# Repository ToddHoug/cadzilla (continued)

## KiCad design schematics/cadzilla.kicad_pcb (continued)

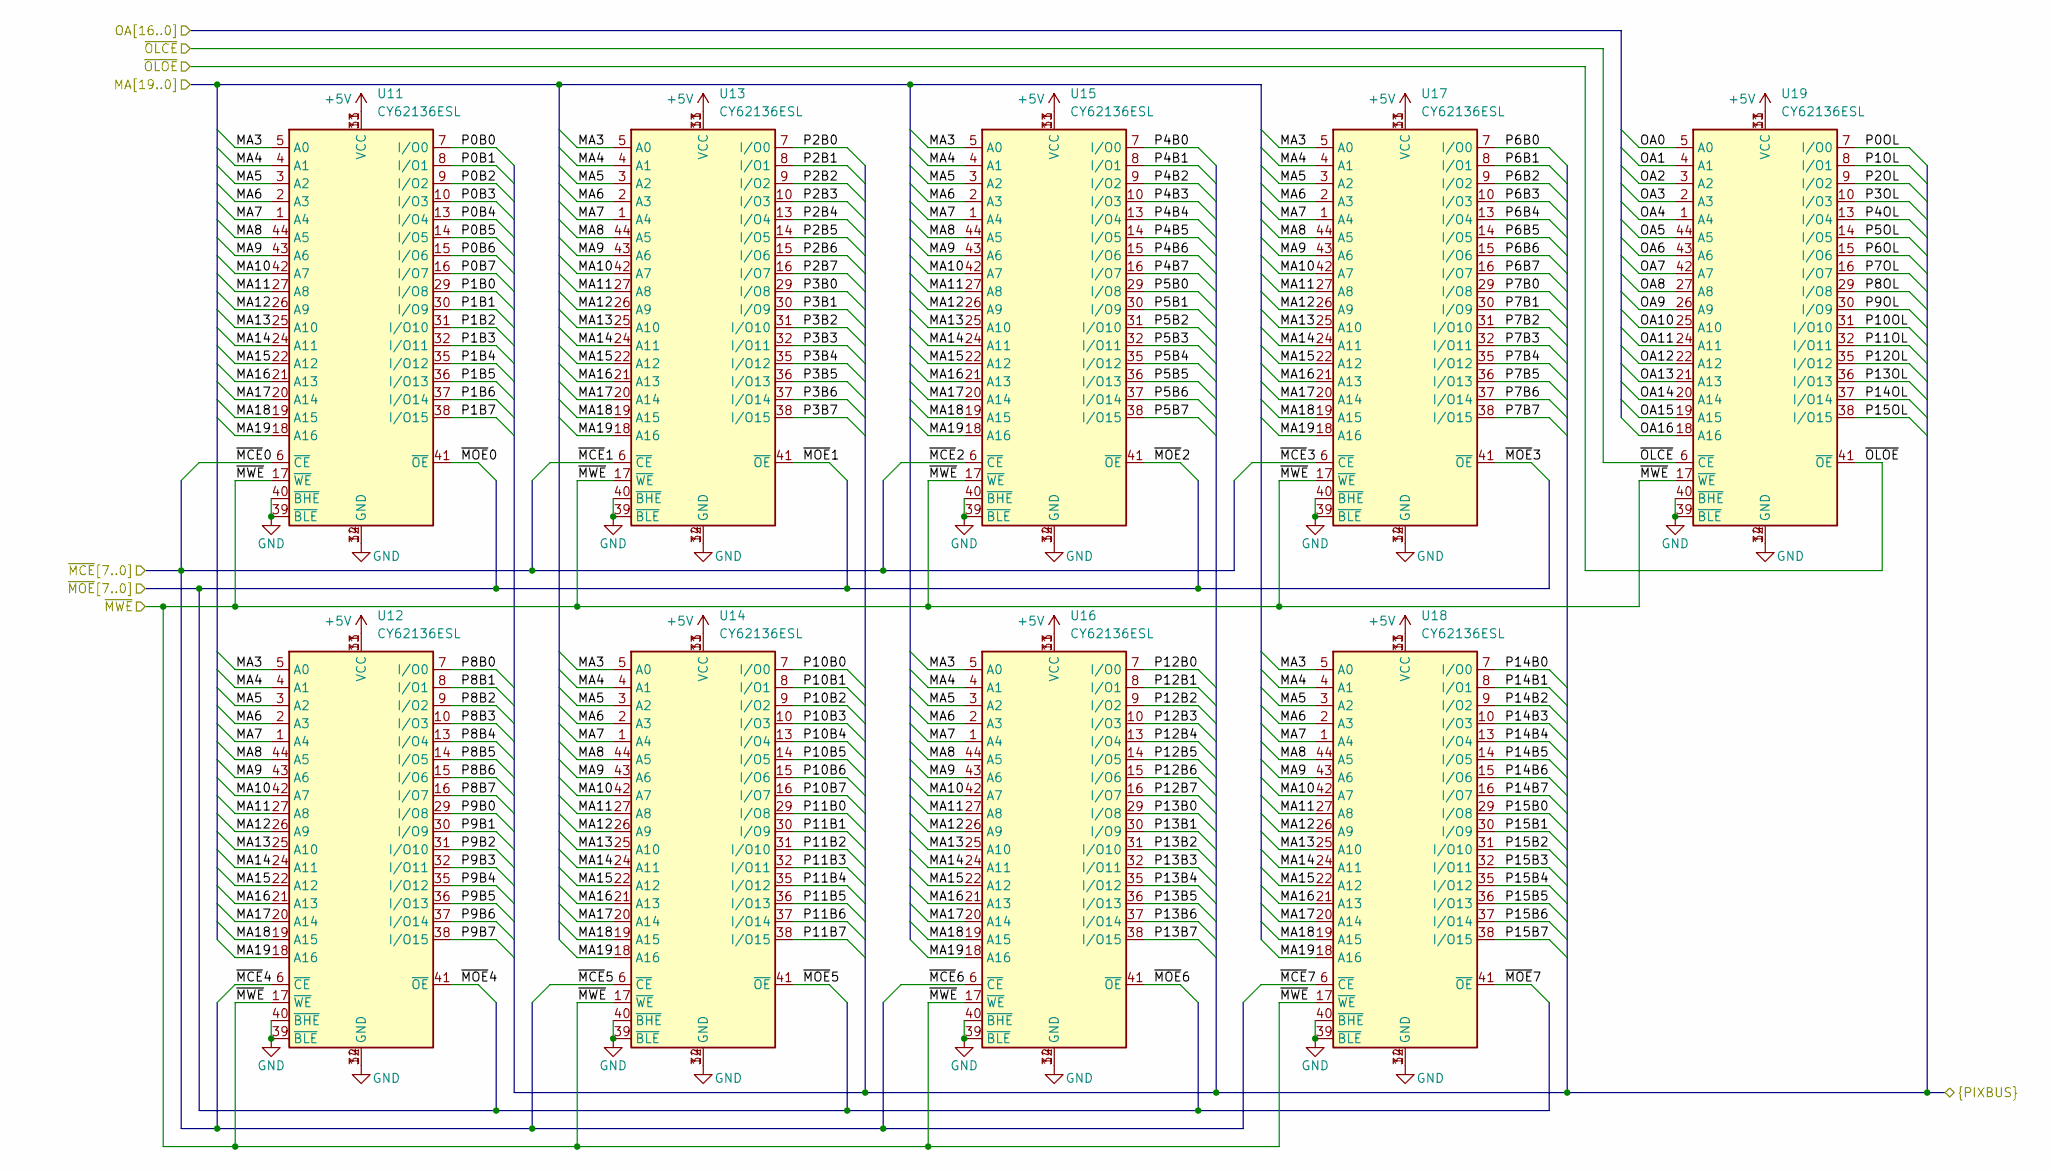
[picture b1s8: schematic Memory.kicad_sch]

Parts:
U11, U12, U13, U14, U15, U16, U17, U18, U19: CY62136ESL; TSOP-II-44_10.16x18.41mm_P0.8mm

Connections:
+5V: U11.11 (VCC), U11.33 (VCC), U12.11 (VCC), U12.33 (VCC), U13.11 (VCC), U13.33 (VCC), U14.11 (VCC), U14.33 (VCC), U15.11 (VCC), U15.33 (VCC), U16.11 (VCC), U16.33 (VCC), U17.11 (VCC), U17.33 (VCC), U18.11 (VCC), U18.33 (VCC), U19.11 (VCC), U19.33 (VCC); also elsewhere on the board
/Data Buffers/P0B0: U11.7 (I/O0); also elsewhere on the board
/Data Buffers/P0B1: U11.8 (I/O1); also elsewhere on the board
/Data Buffers/P0B2: U11.9 (I/O2); also elsewhere on the board
/Data Buffers/P0B3: U11.10 (I/O3); also elsewhere on the board
/Data Buffers/P0B4: U11.13 (I/O4); also elsewhere on the board
/Data Buffers/P0B5: U11.14 (I/O5); also elsewhere on the board
/Data Buffers/P0B6: U11.15 (I/O6); also elsewhere on the board
/Data Buffers/P0B7: U11.16 (I/O7); also elsewhere on the board
/Data Buffers/P0OL: U19.7 (I/O0); also elsewhere on the board
/Data Buffers/P1B0: U11.29 (I/O8); also elsewhere on the board
/Data Buffers/P1B1: U11.30 (I/O9); also elsewhere on the board
/Data Buffers/P1B2: U11.31 (I/O10); also elsewhere on the board
/Data Buffers/P1B3: U11.32 (I/O11); also elsewhere on the board
/Data Buffers/P1B4: U11.35 (I/O12); also elsewhere on the board
/Data Buffers/P1B5: U11.36 (I/O13); also elsewhere on the board
/Data Buffers/P1B6: U11.37 (I/O14); also elsewhere on the board
/Data Buffers/P1B7: U11.38 (I/O15); also elsewhere on the board
/Data Buffers/P1OL: U19.8 (I/O1); also elsewhere on the board
/Data Buffers/P2B0: U13.7 (I/O0); also elsewhere on the board
/Data Buffers/P2B1: U13.8 (I/O1); also elsewhere on the board
/Data Buffers/P2B2: U13.9 (I/O2); also elsewhere on the board
/Data Buffers/P2B3: U13.10 (I/O3); also elsewhere on the board
/Data Buffers/P2B4: U13.13 (I/O4); also elsewhere on the board
/Data Buffers/P2B5: U13.14 (I/O5); also elsewhere on the board
/Data Buffers/P2B6: U13.15 (I/O6); also elsewhere on the board
/Data Buffers/P2B7: U13.16 (I/O7); also elsewhere on the board
/Data Buffers/P2OL: U19.9 (I/O2); also elsewhere on the board
/Data Buffers/P3B0: U13.29 (I/O8); also elsewhere on the board
/Data Buffers/P3B1: U13.30 (I/O9); also elsewhere on the board
/Data Buffers/P3B2: U13.31 (I/O10); also elsewhere on the board
/Data Buffers/P3B3: U13.32 (I/O11); also elsewhere on the board
/Data Buffers/P3B4: U13.35 (I/O12); also elsewhere on the board
/Data Buffers/P3B5: U13.36 (I/O13); also elsewhere on the board
/Data Buffers/P3B6: U13.37 (I/O14); also elsewhere on the board
/Data Buffers/P3B7: U13.38 (I/O15); also elsewhere on the board
/Data Buffers/P3OL: U19.10 (I/O3); also elsewhere on the board
/Data Buffers/P4B0: U15.7 (I/O0); also elsewhere on the board
/Data Buffers/P4B1: U15.8 (I/O1); also elsewhere on the board
/Data Buffers/P4B2: U15.9 (I/O2); also elsewhere on the board
/Data Buffers/P4B3: U15.10 (I/O3); also elsewhere on the board
/Data Buffers/P4B4: U15.13 (I/O4); also elsewhere on the board
/Data Buffers/P4B5: U15.14 (I/O5); also elsewhere on the board
/Data Buffers/P4B6: U15.15 (I/O6); also elsewhere on the board
/Data Buffers/P4B7: U15.16 (I/O7); also elsewhere on the board
/Data Buffers/P4OL: U19.13 (I/O4); also elsewhere on the board
/Data Buffers/P5B0: U15.29 (I/O8); also elsewhere on the board
/Data Buffers/P5B1: U15.30 (I/O9); also elsewhere on the board
/Data Buffers/P5B2: U15.31 (I/O10); also elsewhere on the board
/Data Buffers/P5B3: U15.32 (I/O11); also elsewhere on the board
/Data Buffers/P5B4: U15.35 (I/O12); also elsewhere on the board
/Data Buffers/P5B5: U15.36 (I/O13); also elsewhere on the board
/Data Buffers/P5B6: U15.37 (I/O14); also elsewhere on the board
/Data Buffers/P5B7: U15.38 (I/O15); also elsewhere on the board
/Data Buffers/P5OL: U19.14 (I/O5); also elsewhere on the board
/Data Buffers/P6B0: U17.7 (I/O0); also elsewhere on the board
/Data Buffers/P6B1: U17.8 (I/O1); also elsewhere on the board
/Data Buffers/P6B2: U17.9 (I/O2); also elsewhere on the board
/Data Buffers/P6B3: U17.10 (I/O3); also elsewhere on the board
/Data Buffers/P6B4: U17.13 (I/O4); also elsewhere on the board
/Data Buffers/P6B5: U17.14 (I/O5); also elsewhere on the board
/Data Buffers/P6B6: U17.15 (I/O6); also elsewhere on the board
/Data Buffers/P6B7: U17.16 (I/O7); also elsewhere on the board
/Data Buffers/P6OL: U19.15 (I/O6); also elsewhere on the board
/Data Buffers/P7B0: U17.29 (I/O8); also elsewhere on the board
/Data Buffers/P7B1: U17.30 (I/O9); also elsewhere on the board
/Data Buffers/P7B2: U17.31 (I/O10); also elsewhere on the board
/Data Buffers/P7B3: U17.32 (I/O11); also elsewhere on the board
/Data Buffers/P7B4: U17.35 (I/O12); also elsewhere on the board
/Data Buffers/P7B5: U17.36 (I/O13); also elsewhere on the board
/Data Buffers/P7B6: U17.37 (I/O14); also elsewhere on the board
/Data Buffers/P7B7: U17.38 (I/O15); also elsewhere on the board
/Data Buffers/P7OL: U19.16 (I/O7); also elsewhere on the board
/Data Buffers/P8B0: U12.7 (I/O0); also elsewhere on the board
/Data Buffers/P8B1: U12.8 (I/O1); also elsewhere on the board
/Data Buffers/P8B2: U12.9 (I/O2); also elsewhere on the board
/Data Buffers/P8B3: U12.10 (I/O3); also elsewhere on the board
/Data Buffers/P8B4: U12.13 (I/O4); also elsewhere on the board
/Data Buffers/P8B5: U12.14 (I/O5); also elsewhere on the board
/Data Buffers/P8B6: U12.15 (I/O6); also elsewhere on the board
/Data Buffers/P8B7: U12.16 (I/O7); also elsewhere on the board
/Data Buffers/P8OL: U19.29 (I/O8); also elsewhere on the board
/Data Buffers/P9B0: U12.29 (I/O8); also elsewhere on the board
/Data Buffers/P9B1: U12.30 (I/O9); also elsewhere on the board
/Data Buffers/P9B2: U12.31 (I/O10); also elsewhere on the board
/Data Buffers/P9B3: U12.32 (I/O11); also elsewhere on the board
/Data Buffers/P9B4: U12.35 (I/O12); also elsewhere on the board
/Data Buffers/P9B5: U12.36 (I/O13); also elsewhere on the board
/Data Buffers/P9B6: U12.37 (I/O14); also elsewhere on the board
/Data Buffers/P9B7: U12.38 (I/O15); also elsewhere on the board
/Data Buffers/P9OL: U19.30 (I/O9); also elsewhere on the board
/Data Buffers/P10B0: U14.7 (I/O0); also elsewhere on the board
/Data Buffers/P10B1: U14.8 (I/O1); also elsewhere on the board
/Data Buffers/P10B2: U14.9 (I/O2); also elsewhere on the board
/Data Buffers/P10B3: U14.10 (I/O3); also elsewhere on the board
/Data Buffers/P10B4: U14.13 (I/O4); also elsewhere on the board
/Data Buffers/P10B5: U14.14 (I/O5); also elsewhere on the board
/Data Buffers/P10B6: U14.15 (I/O6); also elsewhere on the board
/Data Buffers/P10B7: U14.16 (I/O7); also elsewhere on the board
/Data Buffers/P10OL: U19.31 (I/O10); also elsewhere on the board
/Data Buffers/P11B0: U14.29 (I/O8); also elsewhere on the board
/Data Buffers/P11B1: U14.30 (I/O9); also elsewhere on the board
/Data Buffers/P11B2: U14.31 (I/O10); also elsewhere on the board
/Data Buffers/P11B3: U14.32 (I/O11); also elsewhere on the board
/Data Buffers/P11B4: U14.35 (I/O12); also elsewhere on the board
/Data Buffers/P11B5: U14.36 (I/O13); also elsewhere on the board
/Data Buffers/P11B6: U14.37 (I/O14); also elsewhere on the board
/Data Buffers/P11B7: U14.38 (I/O15); also elsewhere on the board
/Data Buffers/P11OL: U19.32 (I/O11); also elsewhere on the board
/Data Buffers/P12B0: U16.7 (I/O0); also elsewhere on the board
/Data Buffers/P12B1: U16.8 (I/O1); also elsewhere on the board
/Data Buffers/P12B2: U16.9 (I/O2); also elsewhere on the board
/Data Buffers/P12B3: U16.10 (I/O3); also elsewhere on the board
/Data Buffers/P12B4: U16.13 (I/O4); also elsewhere on the board
/Data Buffers/P12B5: U16.14 (I/O5); also elsewhere on the board
/Data Buffers/P12B6: U16.15 (I/O6); also elsewhere on the board
/Data Buffers/P12B7: U16.16 (I/O7); also elsewhere on the board
/Data Buffers/P12OL: U19.35 (I/O12); also elsewhere on the board
/Data Buffers/P13B0: U16.29 (I/O8); also elsewhere on the board
/Data Buffers/P13B1: U16.30 (I/O9); also elsewhere on the board
/Data Buffers/P13B2: U16.31 (I/O10); also elsewhere on the board
/Data Buffers/P13B3: U16.32 (I/O11); also elsewhere on the board
/Data Buffers/P13B4: U16.35 (I/O12); also elsewhere on the board
/Data Buffers/P13B5: U16.36 (I/O13); also elsewhere on the board
/Data Buffers/P13B6: U16.37 (I/O14); also elsewhere on the board
/Data Buffers/P13B7: U16.38 (I/O15); also elsewhere on the board
/Data Buffers/P13OL: U19.36 (I/O13); also elsewhere on the board
/Data Buffers/P14B0: U18.7 (I/O0); also elsewhere on the board
/Data Buffers/P14B1: U18.8 (I/O1); also elsewhere on the board
/Data Buffers/P14B2: U18.9 (I/O2); also elsewhere on the board
/Data Buffers/P14B3: U18.10 (I/O3); also elsewhere on the board
/Data Buffers/P14B4: U18.13 (I/O4); also elsewhere on the board
/Data Buffers/P14B5: U18.14 (I/O5); also elsewhere on the board
/Data Buffers/P14B6: U18.15 (I/O6); also elsewhere on the board
/Data Buffers/P14B7: U18.16 (I/O7); also elsewhere on the board
/Data Buffers/P14OL: U19.37 (I/O14); also elsewhere on the board
/Data Buffers/P15B0: U18.29 (I/O8); also elsewhere on the board
/Data Buffers/P15B1: U18.30 (I/O9); also elsewhere on the board
/Data Buffers/P15B2: U18.31 (I/O10); also elsewhere on the board
/Data Buffers/P15B3: U18.32 (I/O11); also elsewhere on the board
/Data Buffers/P15B4: U18.35 (I/O12); also elsewhere on the board
/Data Buffers/P15B5: U18.36 (I/O13); also elsewhere on the board
/Data Buffers/P15B6: U18.37 (I/O14); also elsewhere on the board
/Data Buffers/P15B7: U18.38 (I/O15); also elsewhere on the board
/Data Buffers/P15OL: U19.38 (I/O15); also elsewhere on the board
/Memory Interface/MA3: U11.5 (A0), U12.5 (A0), U13.5 (A0), U14.5 (A0), U15.5 (A0), U16.5 (A0), U17.5 (A0), U18.5 (A0); also elsewhere on the board
/Memory Interface/MA4: U11.4 (A1), U12.4 (A1), U13.4 (A1), U14.4 (A1), U15.4 (A1), U16.4 (A1), U17.4 (A1), U18.4 (A1); also elsewhere on the board
/Memory Interface/MA5: U11.3 (A2), U12.3 (A2), U13.3 (A2), U14.3 (A2), U15.3 (A2), U16.3 (A2), U17.3 (A2), U18.3 (A2); also elsewhere on the board
/Memory Interface/MA6: U11.2 (A3), U12.2 (A3), U13.2 (A3), U14.2 (A3), U15.2 (A3), U16.2 (A3), U17.2 (A3), U18.2 (A3); also elsewhere on the board
/Memory Interface/MA7: U11.1 (A4), U12.1 (A4), U13.1 (A4), U14.1 (A4), U15.1 (A4), U16.1 (A4), U17.1 (A4), U18.1 (A4); also elsewhere on the board
/Memory Interface/MA8: U11.44 (A5), U12.44 (A5), U13.44 (A5), U14.44 (A5), U15.44 (A5), U16.44 (A5), U17.44 (A5), U18.44 (A5); also elsewhere on the board
/Memory Interface/MA9: U11.43 (A6), U12.43 (A6), U13.43 (A6), U14.43 (A6), U15.43 (A6), U16.43 (A6), U17.43 (A6), U18.43 (A6); also elsewhere on the board
/Memory Interface/MA10: U11.42 (A7), U12.42 (A7), U13.42 (A7), U14.42 (A7), U15.42 (A7), U16.42 (A7), U17.42 (A7), U18.42 (A7); also elsewhere on the board
/Memory Interface/MA11: U11.27 (A8), U12.27 (A8), U13.27 (A8), U14.27 (A8), U15.27 (A8), U16.27 (A8), U17.27 (A8), U18.27 (A8); also elsewhere on the board
/Memory Interface/MA12: U11.26 (A9), U12.26 (A9), U13.26 (A9), U14.26 (A9), U15.26 (A9), U16.26 (A9), U17.26 (A9), U18.26 (A9); also elsewhere on the board
/Memory Interface/MA13: U11.25 (A10), U12.25 (A10), U13.25 (A10), U14.25 (A10), U15.25 (A10), U16.25 (A10), U17.25 (A10), U18.25 (A10); also elsewhere on the board
/Memory Interface/MA14: U11.24 (A11), U12.24 (A11), U13.24 (A11), U14.24 (A11), U15.24 (A11), U16.24 (A11), U17.24 (A11), U18.24 (A11); also elsewhere on the board
/Memory Interface/MA15: U11.22 (A12), U12.22 (A12), U13.22 (A12), U14.22 (A12), U15.22 (A12), U16.22 (A12), U17.22 (A12), U18.22 (A12); also elsewhere on the board
/Memory Interface/MA16: U11.21 (A13), U12.21 (A13), U13.21 (A13), U14.21 (A13), U15.21 (A13), U16.21 (A13), U17.21 (A13), U18.21 (A13); also elsewhere on the board
/Memory Interface/MA17: U11.20 (A14), U12.20 (A14), U13.20 (A14), U14.20 (A14), U15.20 (A14), U16.20 (A14), U17.20 (A14), U18.20 (A14); also elsewhere on the board
/Memory Interface/MA18: U11.19 (A15), U12.19 (A15), U13.19 (A15), U14.19 (A15), U15.19 (A15), U16.19 (A15), U17.19 (A15), U18.19 (A15); also elsewhere on the board
/Memory Interface/MA19: U11.18 (A16), U12.18 (A16), U13.18 (A16), U14.18 (A16), U15.18 (A16), U16.18 (A16), U17.18 (A16), U18.18 (A16); also elsewhere on the board
/Memory Interface/OA0: U19.5 (A0); also elsewhere on the board
/Memory Interface/OA1: U19.4 (A1); also elsewhere on the board
/Memory Interface/OA2: U19.3 (A2); also elsewhere on the board
/Memory Interface/OA3: U19.2 (A3); also elsewhere on the board
/Memory Interface/OA4: U19.1 (A4); also elsewhere on the board
/Memory Interface/OA5: U19.44 (A5); also elsewhere on the board
/Memory Interface/OA6: U19.43 (A6); also elsewhere on the board
/Memory Interface/OA7: U19.42 (A7); also elsewhere on the board
/Memory Interface/OA8: U19.27 (A8); also elsewhere on the board
/Memory Interface/OA9: U19.26 (A9); also elsewhere on the board
/Memory Interface/OA10: U19.25 (A10); also elsewhere on the board
/Memory Interface/OA11: U19.24 (A11); also elsewhere on the board
/Memory Interface/OA12: U19.22 (A12); also elsewhere on the board
/Memory Interface/OA13: U19.21 (A13); also elsewhere on the board
/Memory Interface/OA14: U19.20 (A14); also elsewhere on the board
/Memory Interface/OA15: U19.19 (A15); also elsewhere on the board
/Memory Interface/OA16: U19.18 (A16); also elsewhere on the board
/Memory Interface/~MCE0: U11.6 (~CE); also elsewhere on the board
/Memory Interface/~MCE1: U13.6 (~CE); also elsewhere on the board
/Memory Interface/~MCE2: U15.6 (~CE); also elsewhere on the board
/Memory Interface/~MCE3: U17.6 (~CE); also elsewhere on the board
/Memory Interface/~MCE4: U12.6 (~CE); also elsewhere on the board
/Memory Interface/~MCE5: U14.6 (~CE); also elsewhere on the board
/Memory Interface/~MCE6: U16.6 (~CE); also elsewhere on the board
/Memory Interface/~MCE7: U18.6 (~CE); also elsewhere on the board
/Memory Interface/~MOE0: U11.41 (~OE); also elsewhere on the board
/Memory Interface/~MOE1: U13.41 (~OE); also elsewhere on the board
/Memory Interface/~MOE2: U15.41 (~OE); also elsewhere on the board
/Memory Interface/~MOE3: U17.41 (~OE); also elsewhere on the board
/Memory Interface/~MOE4: U12.41 (~OE); also elsewhere on the board
/Memory Interface/~MOE5: U14.41 (~OE); also elsewhere on the board
/Memory Interface/~MOE6: U16.41 (~OE); also elsewhere on the board
/Memory Interface/~MOE7: U18.41 (~OE); also elsewhere on the board
/Memory Interface/~MWE: U11.17 (~WE), U12.17 (~WE), U13.17 (~WE), U14.17 (~WE), U15.17 (~WE), U16.17 (~WE), U17.17 (~WE), U18.17 (~WE), U19.17 (~WE); also elsewhere on the board
/Memory Interface/~OLCE: U19.6 (~CE); also elsewhere on the board
/Memory Interface/~OLOE: U19.41 (~OE); also elsewhere on the board
GND: U11.12 (GND), U11.34 (GND), U11.39 (~BLE), U11.40 (~BHE), U12.12 (GND), U12.34 (GND), U12.39 (~BLE), U12.40 (~BHE), U13.12 (GND), U13.34 (GND), U13.39 (~BLE), U13.40 (~BHE), U14.12 (GND), U14.34 (GND), U14.39 (~BLE), U14.40 (~BHE), U15.12 (GND), U15.34 (GND), U15.39 (~BLE), U15.40 (~BHE), U16.12 (GND), U16.34 (GND), U16.39 (~BLE), U16.40 (~BHE), U17.12 (GND), U17.34 (GND), U17.39 (~BLE), U17.40 (~BHE), U18.12 (GND), U18.34 (GND), U18.39 (~BLE), U18.40 (~BHE), U19.12 (GND), U19.34 (GND), U19.39 (~BLE), U19.40 (~BHE); also elsewhere on the board

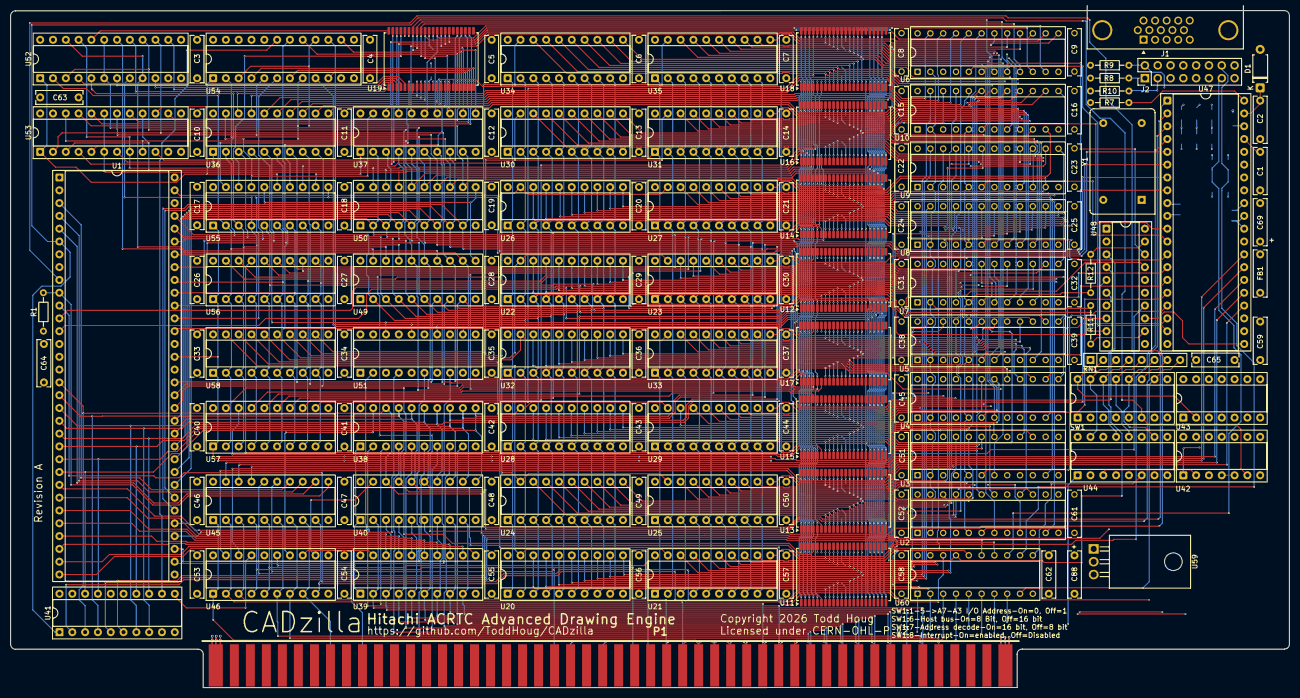
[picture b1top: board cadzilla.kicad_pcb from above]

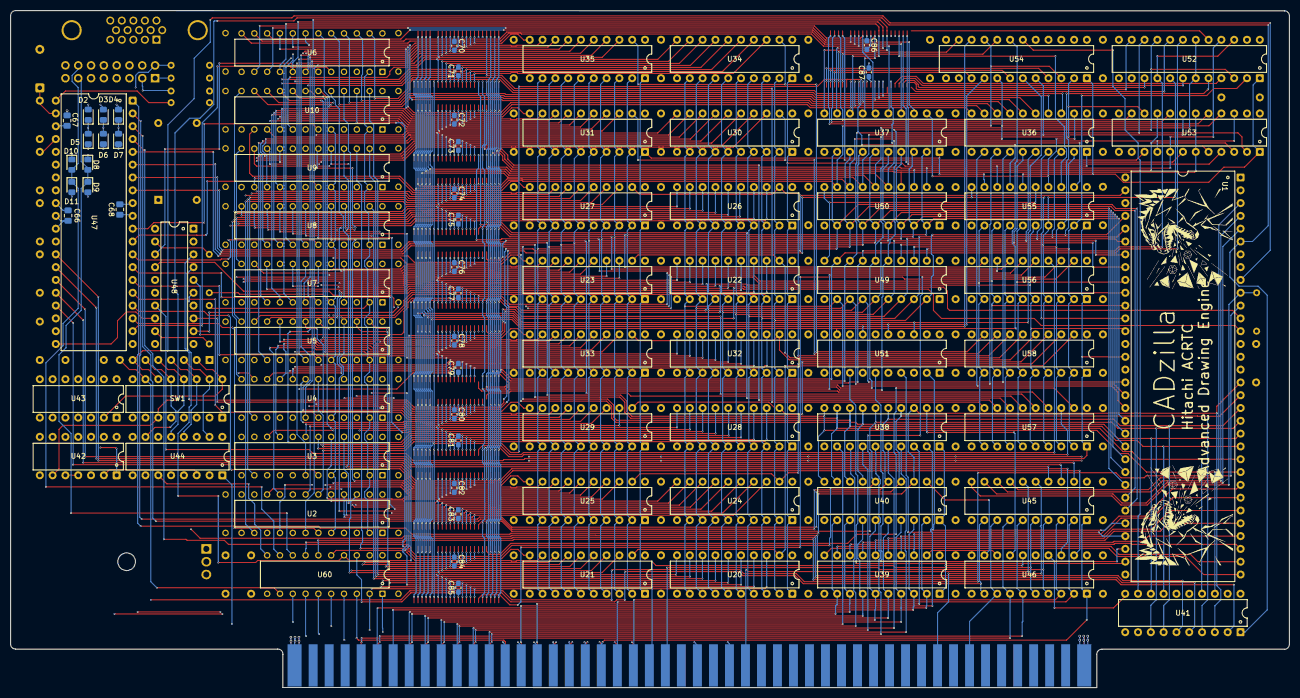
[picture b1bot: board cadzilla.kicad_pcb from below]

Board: 6 copper layers, 253.6 x 134.2 mm, 172 parts (31 on the bottom side), 361 nets.

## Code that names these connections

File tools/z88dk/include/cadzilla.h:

/*
 * SPDX-License-Identifier: GPL-3.0-or-later
 * Copyright (C) 2026 Todd Houg
 *
 * cadzilla.h -- the CADzilla board's I/O ports, for C programs built with
 * z88dk's zcc (tools/z88dk/zccbuild.sh puts this directory on the include
 * path of every zcc project: #include <cadzilla.h>).
 *
 * Sources: docs/cadzilla-manual.pdf (I/O map, MODE register, SW1), the
 * U45/U46/U60 decode equations in pld/src/, and the HD63484 and Bt453
 * datasheets in docs/datasheets/. Nothing here depends on czgfx.
 *
 * Every port is an __sfr: reading or assigning it compiles to ONE inline
 * IN or OUT instruction on the 8080, 8085 and Z80 -- no call, no shared
 * state, safe to use from main-line code and interrupt handlers alike:
 *
 *     unsigned char sr = CZ_ACRTC_SR;      // in  a,(CZ_BASE+0)
 *     CZ_MODE = CZ_MODE_HSPOL;             // out (CZ_BASE+1),a
 *
 * Two cautions, both about sequences rather than single accesses:
 *   - Polling loops: sccz80 widens the test around an __sfr read to 16 bits
 *     and calls library helpers on every pass. Poll in a .Z88 function
 *     instead (tools/z88dk/README.md, "Port I/O").
 *   - Multi-access sequences are not atomic: an ACRTC address-register write
 *     followed by data accesses, or a Bt453 address write followed by its
 *     three R,G,B accesses. If an interrupt handler also talks to the same
 *     chip, disable interrupts around the sequence.
 */
#ifndef CADZILLA_H
#define CADZILLA_H

/*
 * ---- The board's 8-port block ----
 *
 * SW1-1..SW1-5 set I/O address bits 7..3, so the board sits at an 8-port
 * aligned base anywhere in the 8-bit I/O space. 70H is the standard setting;
 * a board strapped elsewhere overrides it for the whole project with
 * -DCZ_BASE=0x.. in zcc.flags.
 */
#ifndef CZ_BASE
#define CZ_BASE 0x70
#endif

/* Port numbers, for code that needs the number itself (e.g. to hand to a
 * .Z88 routine). */
#define CZ_PORT_ACRTC_SR    (CZ_BASE + 0)   /* HD63484 RS=0: status (R)          */
#define CZ_PORT_ACRTC_AR    (CZ_BASE + 0)   /* HD63484 RS=0: address reg (W)     */
#define CZ_PORT_MODE        (CZ_BASE + 1)   /* board MODE register (W only)      */
#define CZ_PORT_ACRTC_DATA  (CZ_BASE + 2)   /* HD63484 RS=1: control reg / FIFO  */
                                            /* +3: reserved, not decoded         */
#define CZ_PORT_DAC_ADDR    (CZ_BASE + 4)   /* Bt453 C1C0=00: address register   */
#define CZ_PORT_DAC_PAL     (CZ_BASE + 5)   /* Bt453 C1C0=01: color palette RAM  */
                                            /* +6: Bt453 C1C0=10, the address    */
                                            /*     register again (use +4)       */
#define CZ_PORT_DAC_OVL     (CZ_BASE + 7)   /* Bt453 C1C0=11: overlay registers  */

/* The ports themselves. */
__sfr __at (CZ_BASE + 0) CZ_ACRTC_SR;       /* read:  ACRTC Status Register      */
__sfr __at (CZ_BASE + 0) CZ_ACRTC_AR;       /* write: ACRTC Address Register     */
__sfr __at (CZ_BASE + 1) CZ_MODE;           /* write only -- keep a copy         */
__sfr __at (CZ_BASE + 2) CZ_ACRTC_DATA;     /* the register AR selects / FIFO    */
__sfr __at (CZ_BASE + 4) CZ_DAC_ADDR;       /* palette / overlay address         */
__sfr __at (CZ_BASE + 5) CZ_DAC_PAL;        /* palette R,G,B (3 accesses each)   */
__sfr __at (CZ_BASE + 7) CZ_DAC_OVL;        /* overlay R,G,B (3 accesses each)   */

/*
 * ---- MODE register (CZ_MODE, write only) ----
 *
 * Board options outside the HD63484's own registers. It can't be read back,
 * so keep the last value written in a variable and update that. Bits 5-7
 * are reserved: write them as 0.
 */
#define CZ_MODE_HSPOL   0x01    /* HSYNC polarity: 0 = positive, 1 = negative pulse  */
#define CZ_MODE_VSPOL   0x02    /* VSYNC polarity: 0 = positive, 1 = negative pulse  */
#define CZ_MODE_AMODE   0x04    /* address mode: 0 = single, 1 = interleaved access  */
#define CZ_MODE_OLEN    0x08    /* overlay: 0 = blanked, 1 = shown over the frame    */
#define CZ_MODE_OLSEL   0x10    /* overlay SRAM half a CHR (drawing) screen          */
                                /* addresses: 0 = lower, 1 = upper 64K words.        */
                                /* Cleared by reset                                  */

/*
 * ---- HD63484 Status Register (CZ_ACRTC_SR) ----
 *
 * After a hardware reset CED, WFR and WFE are 1 and the rest 0.
 */
#define CZ_SR_WFE   0x01    /* write FIFO empty                                   */
#define CZ_SR_WFR   0x02    /* write FIFO ready: room for another write           */
#define CZ_SR_RFR   0x04    /* read FIFO ready: holds data to read                */
#define CZ_SR_RFF   0x08    /* read FIFO full                                     */
#define CZ_SR_LPD   0x10    /* light pen strobe detect (no light pen on board)    */
#define CZ_SR_CED   0x20    /* command end                                        */
#define CZ_SR_ARD   0x40    /* area detect; cleared by RPR or CCR ABT             */
#define CZ_SR_CER   0x80    /* command error; cleared by CCR ABT                  */

/*
 * ---- Bt453 overlay registers ----
 *
 * Write the register's address to CZ_DAC_ADDR, then its red, green and blue
 * values to CZ_DAC_OVL. Address xxxxxx00 is reserved. (Palette entries work
 * the same way: their address 00-FFH, then R,G,B to CZ_DAC_PAL. The address
 * register then steps to the next entry.)
 */
#define CZ_DAC_OVL_COLOR1   0x01
#define CZ_DAC_OVL_COLOR2   0x02
#define CZ_DAC_OVL_COLOR3   0x03

#endif /* CADZILLA_H */
